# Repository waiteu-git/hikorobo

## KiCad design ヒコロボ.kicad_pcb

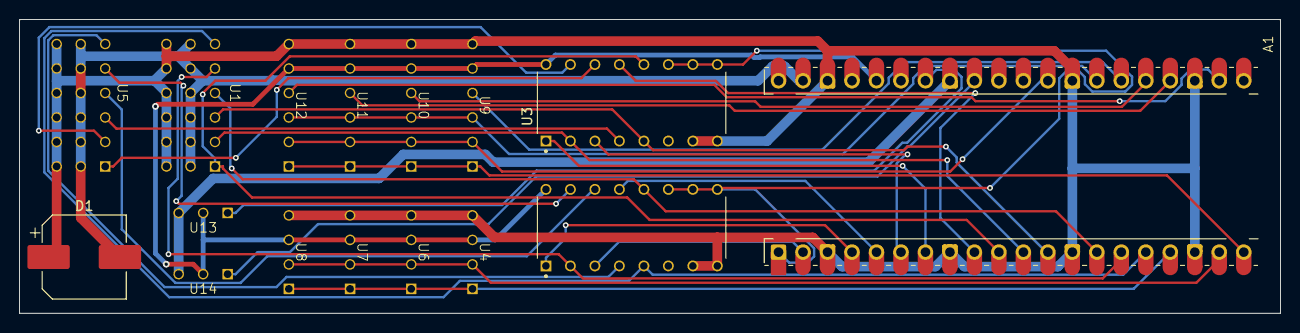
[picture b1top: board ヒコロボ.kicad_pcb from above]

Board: 2 copper layers, 130.8 x 30.5 mm, 16 parts (0 on the bottom side), 34 nets.

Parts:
A1: RaspberryPi_Pico; Raspberry_Pi_Pico
D1: D_Capacitance; CP_Elec_8x10.5
U1: R3106GF; R3106FG
U2, U3: 4053; DIP794W45P254L1969H508Q16
U4, U6, U7, U8: Sensor_I2C_IF
U5: R3106FG_IF; R3106FG
U9, U10, U11, U12: Sensor_SPI_IF
U13, U14: Sensor_Analog_IF

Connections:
+5V: A1.39 (VSYS), D1.2 (A), U1.8 (5v1), U1.9 (5v2), U1.10 (5v3), U1.11 (5v4), U1.12 (5v5), U1.13 (5v6), U5.8 (5v1), U5.9 (5v2), U5.10 (5v3), U5.11 (5v4), U5.12 (5v5), U5.13 (5v6)
GND: A1.3 (GND), A1.8 (GND), A1.13 (GND), A1.18 (GND), A1.23 (GND), A1.28 (GND), A1.38 (GND), D1.1 (K), U1.15 (GND1), U1.16 (GND2), U1.17 (GND3), U1.18 (GND4), U1.19 (GND5), U1.20 (GND6), U2.7 (VEE), U2.8 (VSS), U3.7 (VEE), U3.8 (VSS), U4.4 (GND), U5.15 (GND1), U5.16 (GND2), U5.17 (GND3), U5.18 (GND4), U5.19 (GND5), U5.20 (GND6), U6.4 (GND), U7.4 (GND), U8.4 (GND), U9.6 (GND), U10.6 (GND), U11.6 (GND), U12.6 (GND)
unnamed: A1.36 (3V3), U2.16 (VDD), U3.16 (VDD), U4.3 (VCC), U6.3 (VCC), U7.3 (VCC), U8.3 (VCC), U9.5 (VCC), U10.5 (VCC), U11.5 (VCC), U12.5 (VCC), U13.2 (VCC), U14.2 (VCC)
unnamed: A1.33 (AGND), U13.3 (GND), U14.3 (GND)
unnamed: A1.1 (GPIO0), U2.9 (C), U2.10 (B), U2.11 (A), U3.9 (C), U3.10 (B), U3.11 (A)
unnamed: A1.2 (GPIO1), U2.3 (Z1)
unnamed: A1.4 (GPIO2), U2.1 (Y1)
unnamed: A1.5 (GPIO3), U2.13 (X1)
unnamed: A1.6 (GPIO4), U3.3 (Z1)
unnamed: A1.7 (GPIO5), U3.1 (Y1)
unnamed: A1.9 (GPIO6), U3.13 (X1)
unnamed: A1.10 (GPIO7), U1.1 (Sig1), U3.12 (X0)
unnamed: A1.11 (GPIO8), U1.2 (Sig2), U3.2 (Y0)
unnamed: A1.12 (GPIO9), U1.3 (Sig3), U3.5 (Z0)
unnamed: A1.14 (GPIO10), U1.4 (Sig4), U2.12 (X0)
unnamed: A1.15 (GPIO11), U1.5 (Sig5), U2.2 (Y0)
unnamed: A1.16 (GPIO12), U1.6 (Sig6), U2.5 (Z0)
unnamed: A1.17 (GPIO13), U4.1 (SDA), U6.1 (SDA), U7.1 (SDA), U8.1 (SDA)
unnamed: A1.19 (GPIO14), U4.2 (SCL), U6.2 (SCL), U7.2 (SCL), U8.2 (SCL)
unnamed: A1.20 (GPIO15), U9.1 (MOSI), U10.1 (MOSI), U11.1 (MOSI), U12.1 (MOSI)
unnamed: A1.22 (GPIO17), U12.4 (CS)
unnamed: A1.24 (GPIO18), U11.4 (CS)
unnamed: A1.25 (GPIO19), U10.4 (CS)
unnamed: A1.26 (GPIO20), U9.4 (CS)
unnamed: A1.27 (GPIO21), U9.3 (SCLK), U10.3 (SCLK), U11.3 (SCLK), U12.3 (SCLK)
unnamed: A1.29 (GPIO22), U9.2 (MISO), U10.2 (MISO), U11.2 (MISO), U12.2 (MISO)
unnamed: A1.32 (GPIO27_ADC1), U14.1 (Sig)
unnamed: A1.34 (GPIO28_ADC2), U13.1 (Sig)
unnamed: U2.14 (X), U5.4 (Sig4)
unnamed: U2.15 (Y), U5.5 (Sig5)
unnamed: U2.4 (Z), U5.6 (Sig6)
unnamed: U3.14 (X), U5.1 (Sig1)
unnamed: U3.15 (Y), U5.2 (Sig2)
unnamed: U3.4 (Z), U5.3 (Sig3)

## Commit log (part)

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2026-06-23 fix gitignore location
2026-06-23 remove lock files
2026-06-23 update pcb setting
2026-06-23 pcb changed
2026-06-23 update sensor IF
2026-06-25 wired and clear JLCPCB design rule
